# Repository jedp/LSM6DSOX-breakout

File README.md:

# LSM6DSOX Breakout Board

Three-axis linear accelerometer + gryroscope. Configurable as I2C or SPI.

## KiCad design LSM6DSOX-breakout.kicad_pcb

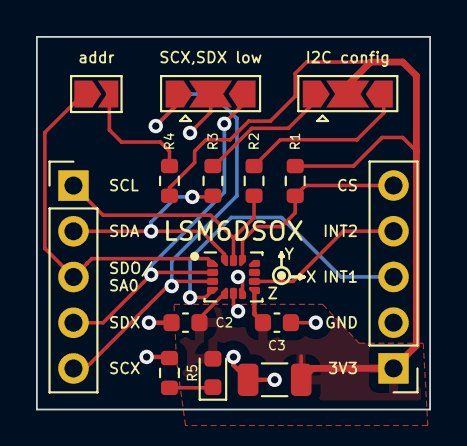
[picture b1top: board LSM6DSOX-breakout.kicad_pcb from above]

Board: 2 copper layers, 21.8 x 20.7 mm, 15 parts (0 on the bottom side), 14 nets.

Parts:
C1: 10µ; C_1206_3216Metric
C2, C3: 0.1µ; C_0603_1608Metric
D1: LED PWR; LED_0603_1608Metric
I2C config: I2C EN; SolderJumper-3_P2.0mm_Open_TrianglePad1.0x1.5mm
J1, J2: Conn_01x05_Female; PinHeader_1x05_P2.54mm_Vertical
R1, R4: 100k; R_0603_1608Metric
R2, R3: 10k; R_0603_1608Metric
R5: 1k; R_0603_1608Metric
SCX,SDX low: I2C EN; SolderJumper-3_P2.0mm_Open_TrianglePad1.0x1.5mm
U1: LSM6DS3; LGA-14_3x2.5mm_P0.5mm_LayoutBorder3x4y
addr: I2C ADDR; SolderJumper-2_P1.3mm_Open_TrianglePad1.0x1.5mm

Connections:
+3V3: C1.1, C2.1, C3.1, D1.2 (A), I2C config.2 (C), J2.1, R1.1, R4.1, U1.5 (VDDIO), U1.8 (VDD)
CS: J2.5, R1.2, U1.12 (CS)
GND: C1.2, C2.2, C3.2, J2.2, R5.1, SCX,SDX low.2 (C), U1.6 (GND), U1.7 (GND)
INT1: J2.3, U1.4 (INT1)
INT2: J2.4, U1.9 (INT2)
unnamed: D1.1 (K), R5.2
unnamed: I2C config.1 (A), R3.1
unnamed: I2C config.3 (B), R2.1
unnamed: R4.2, addr.2 (B)
SCL: J1.1, R2.2, U1.13 (SCL)
SCX: J1.5, SCX,SDX low.1 (A), U1.3 (SCX)
SDA: J1.2, R3.2, U1.14 (SDA)
SDO/SA0: J1.3, U1.1 (SDO/SA0), addr.1 (A)
SDX: J1.4, SCX,SDX low.3 (B), U1.2 (SDX)

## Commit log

2023-03-01 LSM6DSOX Breakout board
